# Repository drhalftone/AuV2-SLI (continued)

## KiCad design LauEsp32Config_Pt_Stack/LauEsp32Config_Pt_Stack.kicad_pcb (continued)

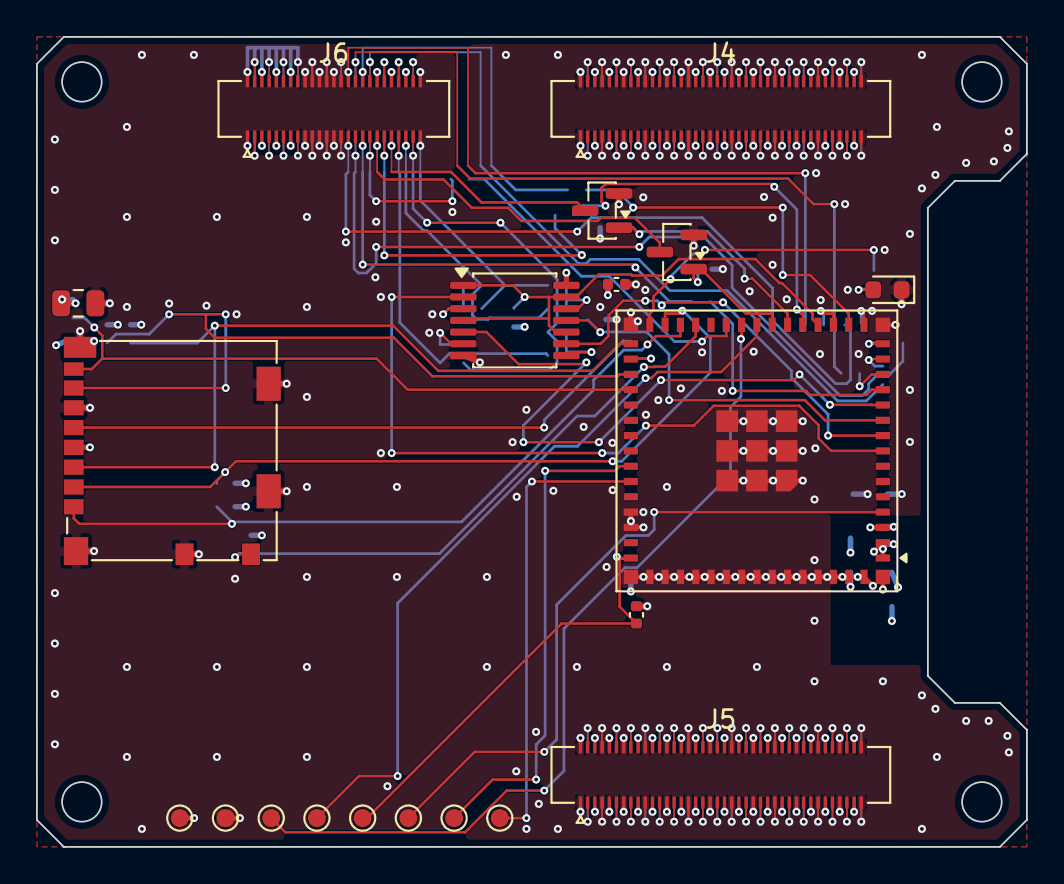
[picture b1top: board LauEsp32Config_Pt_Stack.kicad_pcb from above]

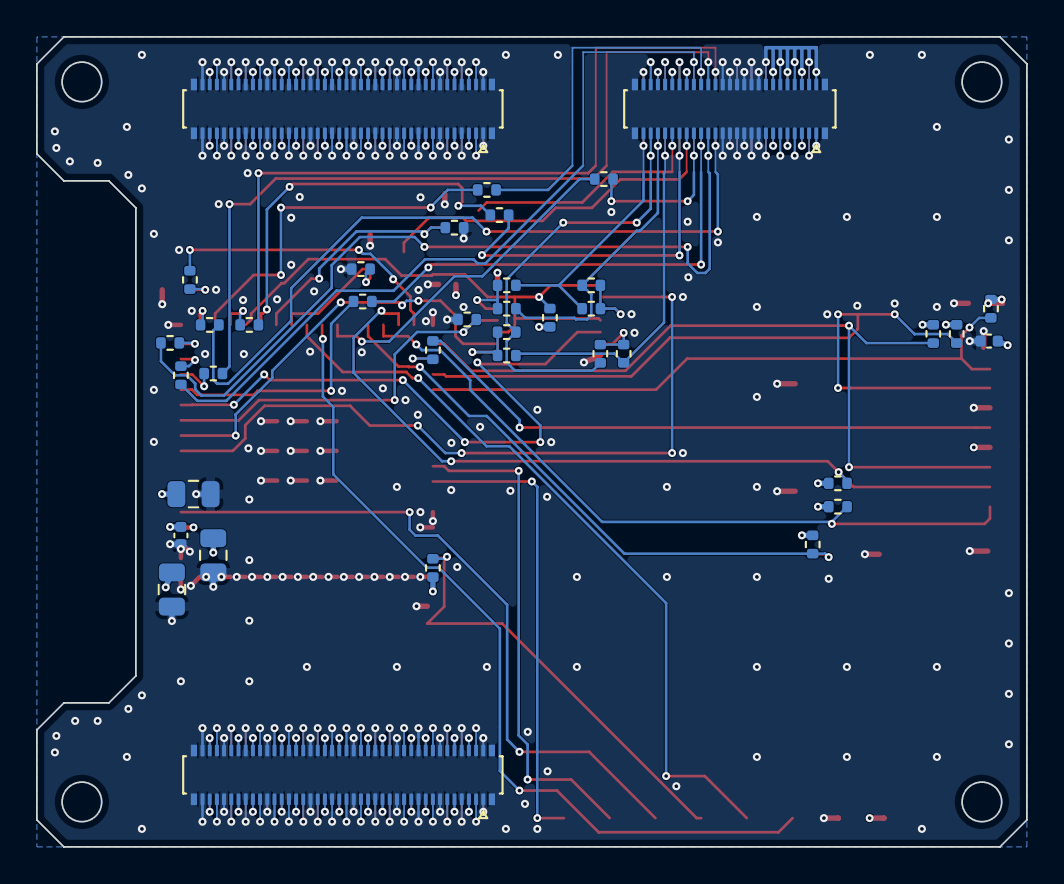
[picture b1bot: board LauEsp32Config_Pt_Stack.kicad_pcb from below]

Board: 4 copper layers, 55.0 x 45.0 mm, 58 parts (38 on the bottom side), 165 nets.

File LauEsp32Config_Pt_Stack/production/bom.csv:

Comment,Designator,Footprint,LCSC Part #
"22u","C1,C2",C_0805_2012Metric,C45783
"10u","C3,C7",C_0805_2012Metric,C15850
"100n","C4,C6,C8",C_0402_1005Metric,C1525
"1u","C5",C_0402_1005Metric,C52923
"Red","D1",LED_0603_1608Metric,C2286
"DF40C-80DP-0.4V(51)","J1,J2",Hirose_DF40C-80DP-0.4V_2x40-1MP_P0.4mm,C294544
"DF40C-50DP-0.4V(51)","J3",Hirose_DF40C-50DP-0.4V_2x25-1MP_P0.4mm,C424645
"DF40HC(4.0)-80DS-0.4V(51)","J4,J5",Hirose_DF40HC(4.0)-80DS-0.4V_2x40_P0.4mm,C5254351
"DF40HC(4.0)-50DS-0.4V(51)","J6",Hirose_DF40HC(4.0)-50DS-0.4V_2x25_P0.4mm,C5338326
"1040310811","J7",microSD_HC_Molex_104031-0811,C585350
"2N7002","Q1,Q2",SOT-23,C8545
"10k","R1,R2,R3,R4,R5,R31,R32,R33,R34,R35,R36",R_0402_1005Metric,C25744
"1k","R6,R7",R_0402_1005Metric,C11702
"0R","R10,R11,R12",R_0402_1005Metric,C17168
"33R","R13,R20,R21,R22,R23,R24,R25,R26,R27,R30",R_0402_1005Metric,C25105
"ESP32-S3-MINI-1U-N8","U1",ESP32-S2-MINI-1U,C2980299
"SN74LVC125APWR","U2",TSSOP-14_4.4x5mm_P0.65mm,C7813

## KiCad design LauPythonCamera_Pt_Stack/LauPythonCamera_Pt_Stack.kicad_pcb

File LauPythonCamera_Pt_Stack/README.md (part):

# LauPythonCamera_Pt_Stack — Design Blueprint

> **STATUS: the board works and is in the merged design.** The sensor is alive,
> aligned and streaming 1280x1024 at 120.000 Hz over the Ft+, concurrently with
> the HDMI/SLI datapath in one bitstream — see
> [`../MERGE_MILESTONES.md`](../MERGE_MILESTONES.md). This document remains the
> design blueprint for the PCB itself.
>
> Known hardware note: the Andon LCC48 socket is effectively unobtainable, so the
> sensor is held by a printed fixture clamping wires to the bottom castellations —
> see [`mech/README.md`](mech/README.md).

> ### Power: §§6.2 and 6.5 were rewritten on 2026-07-18 and now match the board.
>
> **[`../CAMERA_POWER_DESIGN.md`](../CAMERA_POWER_DESIGN.md) remains authoritative** for the
> power tree — full derivation, SPICE verification and BOM. This document is the design
> blueprint; where the two disagree, that one wins.
>
> **What changed, and why it matters historically.** The original power section described a
> "3.3 V tap through ferrites + load switch" tree, built on the premise that the Pt's `+3.3V`
> rail is 3.300 V. **It is 3.278 V** — derivable from Alchitry's own feedback divider
> (R16 = 31.6 kΩ / R15 = 10.2 kΩ into the ADP5052's 0.8 V reference), ±1.5 % → **3.229–3.327 V**.
> That broke the design three ways:
>
> - **`vdd_pix` (3.25–3.35 V) was out of spec** at the rail's low corner, by 21 mV.
> - **`vdd_33` had ~7 mV** of worst-case margin after ferrite and connector IR drop.
> - **The tap made correct power-up sequencing impossible.** `vdd_33` tapped from `+3V3` rises the
>   instant the Pt's rail does, but 1.8 V can only be made by LDO'ing *down from that same rail* —
>   so `vdd_18` always came up **after** `vdd_33`, the forbidden order, on every power-up. That
>   risks latch-up and a dead sensor.
>
> The board uses **boost → LDO**: `+3V3` → TPS61023 boost to 4.45 V → two TPS7A2033 LDOs for
> `vdd_33` and `vdd_pix`, `vdd_18` from a TPS7A2018 off `+3V3` directly, and **two TLV803S
> supervisors** enforcing power-up *and* power-down ordering. **There is no load switch and no
> ferrite on this board.** If you find text saying otherwise, it is stale — report it (§14.6).

Custom Alchitry **element board** carrying an onsemi **PYTHON 1300** global-shutter image
sensor in a **socketed 48-pin LCC**, for the AuV2-SLI structured-light system.

## Status

| | |
|---|---|
| Pin plan | ✅ **Confirmed by Vivado** (§13.1) |
| Whole stack — Pt V2 + Hd + Ft+ + camera | ✅ **Confirmed by Vivado** — 105 ports, no conflicts (§13.2) |
| Schematic | ⚠️ Complete and audited — but the **power tree was rebuilt from scratch** after an audit found it architecturally wrong (§6.5). **Deserves a human read before fab.** |
| Socket footprint | ✅ Built and verified (§12) — **no longer blocked** |
| Stackup / netclasses / DRC rules | ✅ Written (§11), and **calibrated against a real DRC run** (§14.7) |
| **Layout** | ✅ **Routed, reviewed (§14), DRC-clean (0 errors, 0 unconnected), and all three Tier 1 defects are FIXED** — re-verified against the board 2026-08-06. U1 decoupling closed by moving ten caps to the underside beneath the pins; power-section stitching now 13 GND vias; `+3V3_SYS` widened to 0.6 mm with the J3 pins fanned out. Six test points added. **Fab-ready** — two optional single-via redundancy items remain (§15.0), neither a blocker. |
| **Sensor + socket ordered** | ❌ **Do this first** — §15.1. Sensor: **~27-week** factory lead if distributor stock runs out — this is the critical path. Socket: **no stock anywhere**, Andon builds to order in **6–8 weeks**, so it is *not* the driver. |

**Eleven bugs have been found and fixed in this design so far**, including two that would have
destroyed the sensor and two that would have scrapped the board. Every one was a *boundary
crossed without re-deriving*: datasheet frame → KiCad frame, body extent → copper extent,
thermal question → voltage question, logic behaviour → electrical behaviour.

The FPGA side is tool-verified (§13). **The board side is verified only by my own arithmetic.**
The power section in particular has been rewritten and should be read by a human before copper.

---

## 1. What this board is for

The SLI system puts the FPGA **inline on HDMI between the host PC and the projector**
(hence the EDID-merge / HPD re-pulse logic in the main RTL). This board adds the *camera*
half: a 1.3 MP global-shutter sensor whose exposure can be synchronized to the projected
pattern sequence.

Because the camera must capture **in sync** with the projected patterns, HDMI pass-through
and camera capture run **simultaneously**. That constraint drives the entire pin plan below.

---

## 2. Board stack

```
   [ LauPythonCamera_Pt_Stack ]  <- THIS BOARD.  TOP, Bank B (B33-B78), bank 13, VCCO = 2.5 V
 ────────────────────────────────
          Alchitry Pt V2            XC7A100T-2FGG484I, 206 IO, 256 MB DDR3L
 ────────────────────────────────
   [ Sp ]    spacer — clears the Pt's bottom-side capacitors        $14.99
   [ Ft+ ]   bottom  A3-A42 + B3-B24   (3.3 V)   FT601Q USB3, 348 MB/s measured
   [ Sp ]    spacer — micro-HDMI / USB cable clearance              $14.99
   [ Hd  ]   bottom  A45-A78           (3.3 V)   2x micro-HDMI (PC in, projector out)
```

**This board goes on TOP, alone.** Rationale:

- The **Hd's signal pass-through is undocumented** and may terminate a stack. Keeping the
  camera on top means it never has to sit above the Hd, and **this board needs no
  pass-through connectors at all.**
- The 32 multi-voltage pins (the only ones that can run at 2.5 V) exist **only on the top**
  Bank-B connector. There are **zero** multi-voltage pins on the bottom. The camera
  therefore *must* be on top.

A `Br` ($14.99) may substitute for either `Sp`. **Do not use the `Fn`** — its fan-control
solder jumper lands on **B36, a bank-13 pin**, and would consume half of one of our LVDS
pairs.

---

## 3. Why the pin plan works — bank voltages

This is the crux of the design, and it was the one thing that could have sunk the stack.

| Consumer | IO standard | Required VCCO |
|---|---|---|
| Hd (HDMI TMDS) | `TMDS_33` | **3.3 V** |
| Ft+ (FT601 FIFO) | `LVCMOS33` | **3.3 V** |
| **This board (sensor LVDS)** | **`LVDS_25`** | **2.5 V** |

An FPGA bank has exactly one VCCO, so these had to land in different banks. On the Pt V2
they do:

| Bank | VCCO | Pins |
|---|---|---|
| 14, 16, 34, 35 | **hardwired 3.3 V** | Hd and Ft+ live here |
| 15 | 1.35 V | DDR3L (internal) |
| **13** | **switchable 3.3 / 2.5 / 1.8 V** | **top Bank B, B33-B78 — 32 pins / 16 pairs — ALL OURS** |

**Neither the Hd nor the Ft+ places a single pin in bank 13.** Verified against Alchitry's
own constraint sources (`ft_plus_v2.acf`, `hd_v2.acf`, `PtV2TopPin.kt`) and cross-checked
against the official `pt_hd_bottom.xdc` / `pt_ft_plus_bottom.xdc`. The product pages do not
contain this information.

The Ft+ (A3-A42 + B3-B24) and the Hd (A45-A78) are also **mutually disjoint** — they are
designed to coexist. Their only conflict is mechanical (cable clearance), solved by the `Sp`.

### LVDS_25 nuance that forces bank 13

An `LVDS_25` **input** with *external* 100 Ω termination imposes no VCCO requirement and
would work in a 3.3 V bank. But:

- an `LVDS_25` **output** — which we need, to drive `lvds_clock_in±` **into** the sensor — and
- any input using the FPGA's **internal `DIFF_TERM`**

both **require VCCO = 2.5 V**. So bank 13 is mandatory regardless of how we terminate.

> **DANGER.** Alchitry: *"Failing to set the tri-voltage pins correctly could damage the
> FPGA."* See the VBSEL strapping in §6.

---

## 4. Sensor

> **Now fitted (2026-10):** the **colour** `NOIP1SE1300A` (Bayer), in the Andon socket. Same pinout,
> same chip ID (`0x50D0`); the only boot difference is register 2 = `0x0001`.

**`NOIP1SN1300A-QTI`** — PYTHON 1300, monochrome, 4-LVDS output, 48-pin LCC. *(The
originally-specified `-QDI` is discontinued; `-QTI` is the identical sensor with a peel-off
protective foil over the glass — see the ordering note below.)*

| | |
|---|---|
| Resolution / rate | 1280 x 1024, 10-bit, **150 fps** (sensor max; we run a locked **120 Hz** — see *Operating point*) |
| Pixel | 4.8 x 4.8 µm, global shutter |
| Package | 48-pin LCC, **14.22 x 14.22 mm, 1.016 mm pitch**, D263 glass lid |
| Output | 4 LVDS data + 1 LVDS sync + 1 LVDS clock out; 720 Mbps/ch |
| Supplies | `vdd_33` 3.3 V, `vdd_18` 1.8 V, `vdd_pix` 3.3 V (tight: 3.25-3.35 V) |
| Price / lead | ~$139, long factory lead — order early |

**The VITA 1300 (`NOIV1SN1300A`) is pin-for-pin identical** — all 48 pins, both LVDS and
parallel variants — so this board accepts either. PYTHON is preferred: faster, and the VITA
datasheet carries a *"no silicon fix planned"* erratum (first-row blooming, costing 5 rows).

Design the rails to **PYTHON's tighter tolerances** so either part drops in.

> **Order the `-QTI` suffix.** The originally-specified `-QDI` (no protective foil) has been
> discontinued. `-QTI` is the identical PYTHON 1300 sensor but ships with a **peel-off
> protective foil** over the glass — remove it before installing the sensor (handle the glass
> by the edges afterward). The foil is otherwise harmless handling protection, and a bonus:
> its tab points toward pin 1 — a useful orientation aid, since the package has no chamfer/dot (§12).

### Bandwidth check

```
1280 x 1024 x 10 bit x 150 fps  =  245.8 MB/s
Ft+ (FT601Q), BARE LINK 2026-07-31 = 348   MB/s     ->  pattern generator only
Ft+ (FT601Q), END-TO-END 2026-08-17 = 232  MB/s     ->  with camera + DDR running
Ft  (FT600),  datasheet estimate  =  190   MB/s     ->  does NOT fit
```

> **THE TWO Ft+ NUMBERS MEASURE DIFFERENT THINGS, and only one of them is a budget.**
> 348 MB/s is the FT601 fed by a pattern generator — no camera, no DDR, nothing
> competing. With the real pipeline running, the *same* `ft_bench_async.py` measures
> **231.7 MB/s**, because the reader is now sharing one MIG port with the capture
> writer. Sampled while saturated, both ends were at their limit at once: the DDR→USB
> FIFO ran dry 32 % of the time **and** the FT601 back-pressured 40 %.
>
> **Budget against ~232 MB/s.** Using 348 led directly to a build that targeted 120 Hz
> at 16 bpp (314.6 MB/s "with ~10 % margin") and delivered **88 fps**.
>
> The Ft (FT600) number is still an estimate — not measured here.

### Operating point — ACHIEVED 2026-08-17

**1280 × 1024, packed 10-bit, locked 120.000 Hz, exposure settable at runtime.**

```
capture     120.000 Hz   (600,000 wordclk cycles, +/-2 cycles jitter -> ~3 ppm)
delivered   119.8 fps    201 MB/s, 25 CLEAN / 0 padded, ldrop static at 0
alignment   10 of 10 frames agree, r = 1.000
exposure    monotonic 75 us -> 4800 us, no saturation, independent of frame rate
```

Three things had to be true at once, and each was a separate fault:

1. **Dense 10-bit packing** (format 3, 4 px in 5 bytes). At 16 bpp a 120 Hz frame costs
   314.6 MB/s against ~232 available; packed it costs **196.6 MB/s**. 37.5 % of every
   byte moved had been zero padding. Packing goes all the way into DDR, not just onto
   the wire — otherwise the reader still pulls 314.6 MB/s out of DDR, which is the side
   that was already starving.
2. **Frame-start resync in the DDR writer.** Without it, one lost kernel repositioned
   every frame that followed, permanently — the picture rolled in both axes.
3. **The trigger pulse width.** `TRIGGERED=1` paced the sensor at a perfect 120.000 Hz
   while delivering *no pixels at all*, because the pulse width came from an
   **exposure-sweep experiment table that was never gated on `EXPO_SWEEP`**. It cycled
   50 → 6400 µs every eight frames, and 6.4 ms of integration plus 6.86 ms of readout
   does not fit in an 8.33 ms period. It also meant exposure was set by pulse width, so
   `exposure0` did nothing in triggered mode. The trigger is now a fixed 10 µs
   frame-start marker and the sensor integrates for `exposure0`.

#### Usable exposure range at 120 Hz — and a state that needs a reflash to escape

**Maximum exposure is 8243 µs, and the boundary is a cliff, not a slope.** The sensor
cannot integrate for a whole frame period *and* still answer the next trigger, so past
the limit it wedges. Measured against the DELIVERED rate:

```
2026-10-07, with the CDS timing program loaded (the current sensor configuration):
 600..8254 us   121 fps       full rate
      8256 us     0.0 fps     wedges            -> the sensor needs ~78 us after an exposure

before 2026-10-05, without it (kept for history -- NOT valid now):
 600..8280 us   111-122 fps   full rate, ldrop 0 at every setting
      8300 us      0.0 fps    collapses
      8333 us     59.8 fps    every other trigger missed
```

The old 8280 µs figure wedged the sensor once the CDS program went in. The limit is now
`period − 80 µs − 10 µs` (`usb_link.v` publishes it as MAXEXP; `cam_expo_safety.v` enforces it).

> **The status UART cannot see this.** It reports a healthy 120.00 Hz throughout,
> because the FPGA goes on triggering whether or not the sensor answers. Only the
> delivered byte rate shows the truth — the same trap as the throughput-vs-bytes
> lesson in [`ROADMAP.md`](../ROADMAP.md) §6.

> **⚠️ OVER-EXPOSING WEDGES THE SENSOR.** After one setting above the cliff, restoring a
> valid exposure did NOT recover it: `expo_cur` read back correctly and frame_start kept
> arriving at 120.000 Hz, but no frame ever completed (`rdBusy = 0`) and no bytes
> reached USB. A re-arm (opcode 3) did not help either. It took a full FPGA reconfigure
> to re-run the sensor's SPI boot sequence. That is why the cap is now **enforced in the
> FPGA** (`ddr/cam_expo_safety.v`): every exposure command is clamped, the exposure is
> shortened when the rate rises, and the trigger is held while a longer exposure may still
> be in effect. `cam_live.py` takes its slider top from the FPGA's MAXEXP.

> **The 120 Hz is the right RATE but not a locked PHASE.** The trigger comes from the
> FPGA's own 100 MHz crystal, so it drifts against a projector on a different
> oscillator. For structured light that drift is the whole problem — see
> [`ROADMAP.md`](../ROADMAP.md) §6.5 for the external-HDMI-sync plan (vsync-derived
> trigger with a user-programmable phase shift), and the wiring question that gates it.

The Ft+ is **mandatory**. The Ft cannot carry full-rate capture, and the Pt V2's onboard
FT2232HQ is USB 2.0 (JTAG/UART only) — not a data path.

---

## 5. Pin plan

<!-- PIN_TABLE_START -->

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
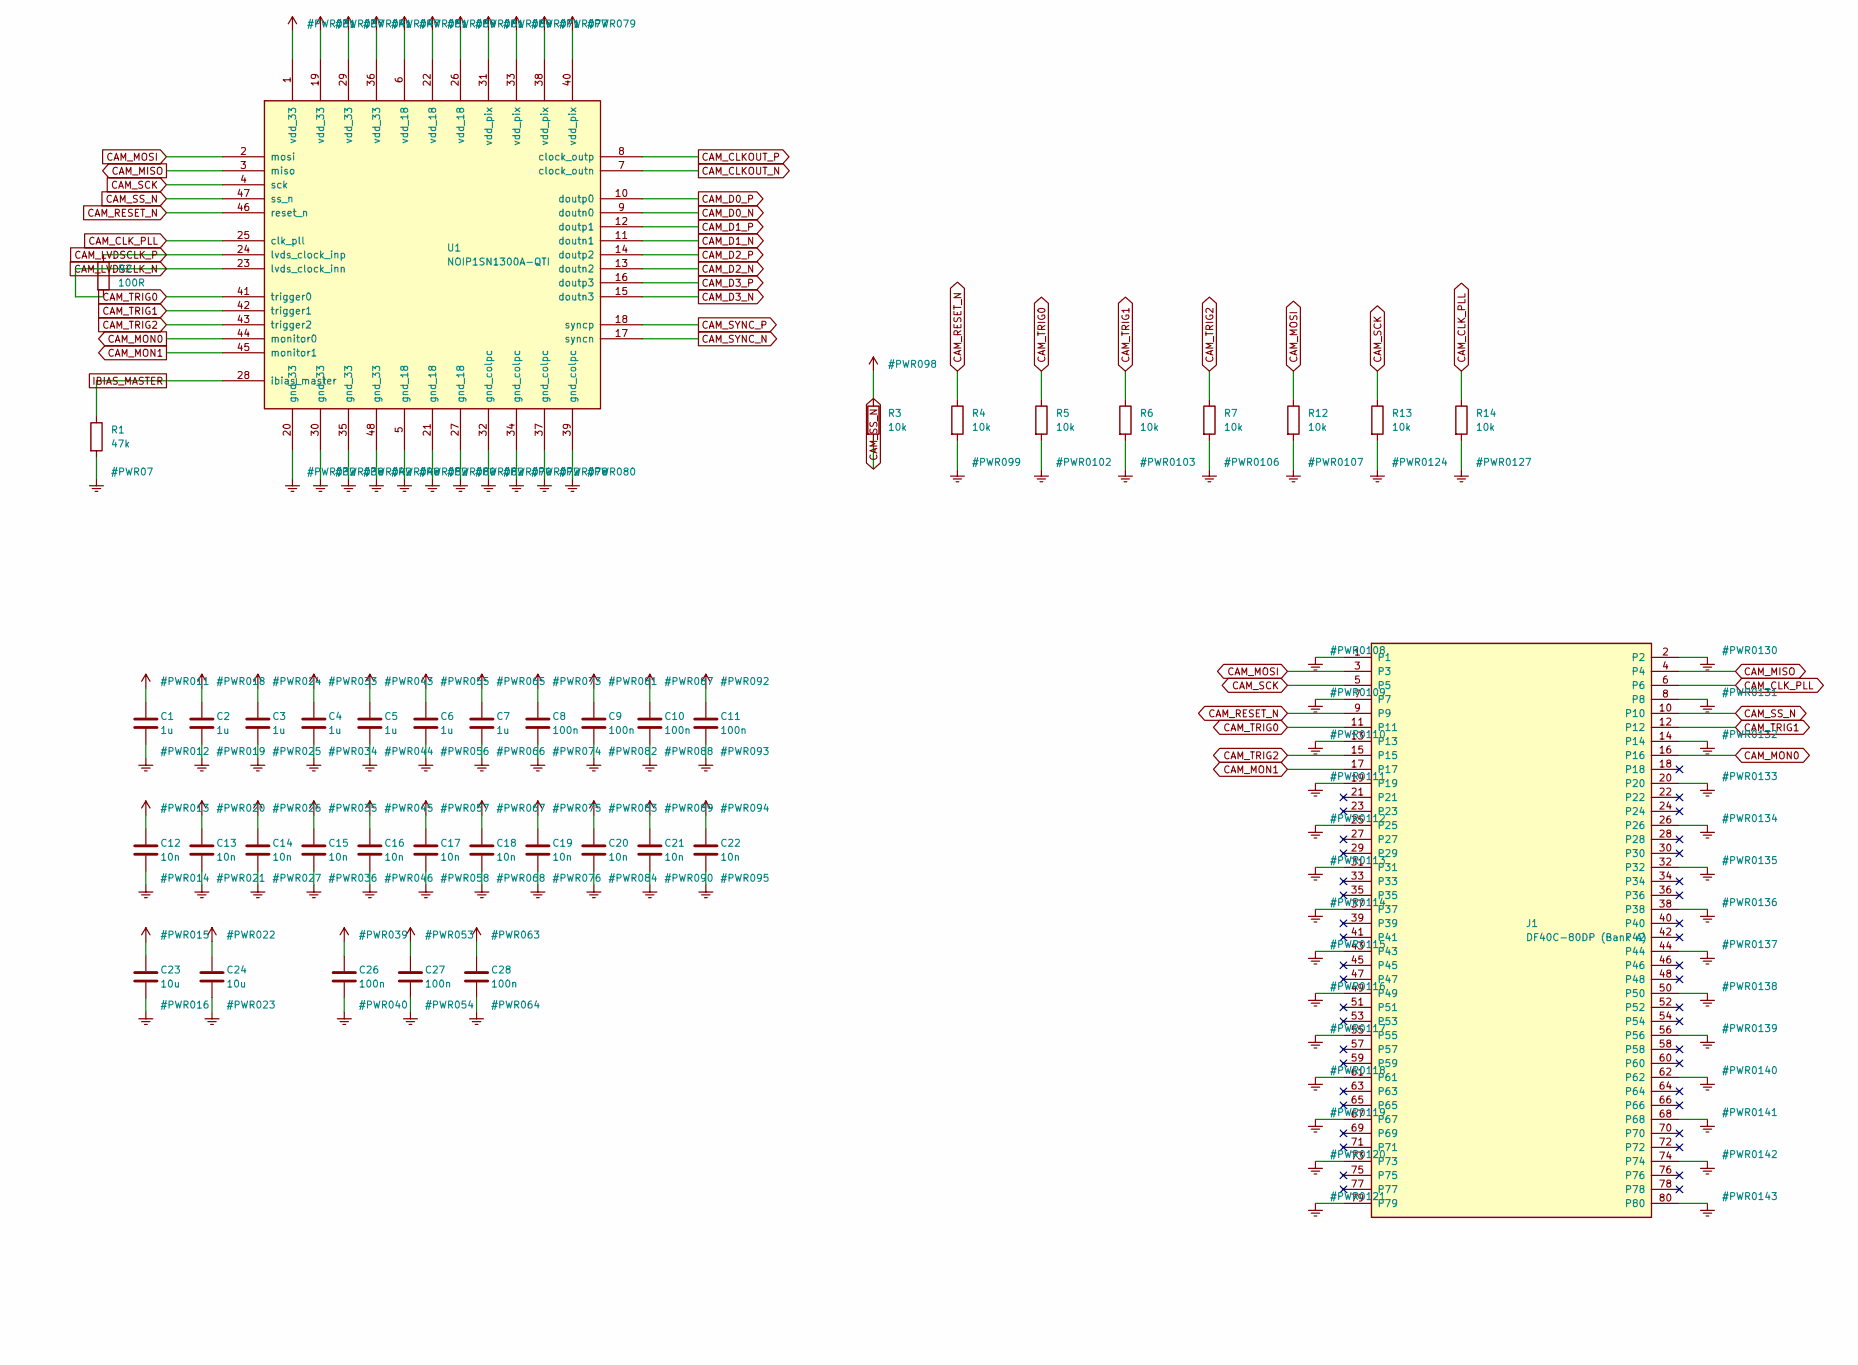
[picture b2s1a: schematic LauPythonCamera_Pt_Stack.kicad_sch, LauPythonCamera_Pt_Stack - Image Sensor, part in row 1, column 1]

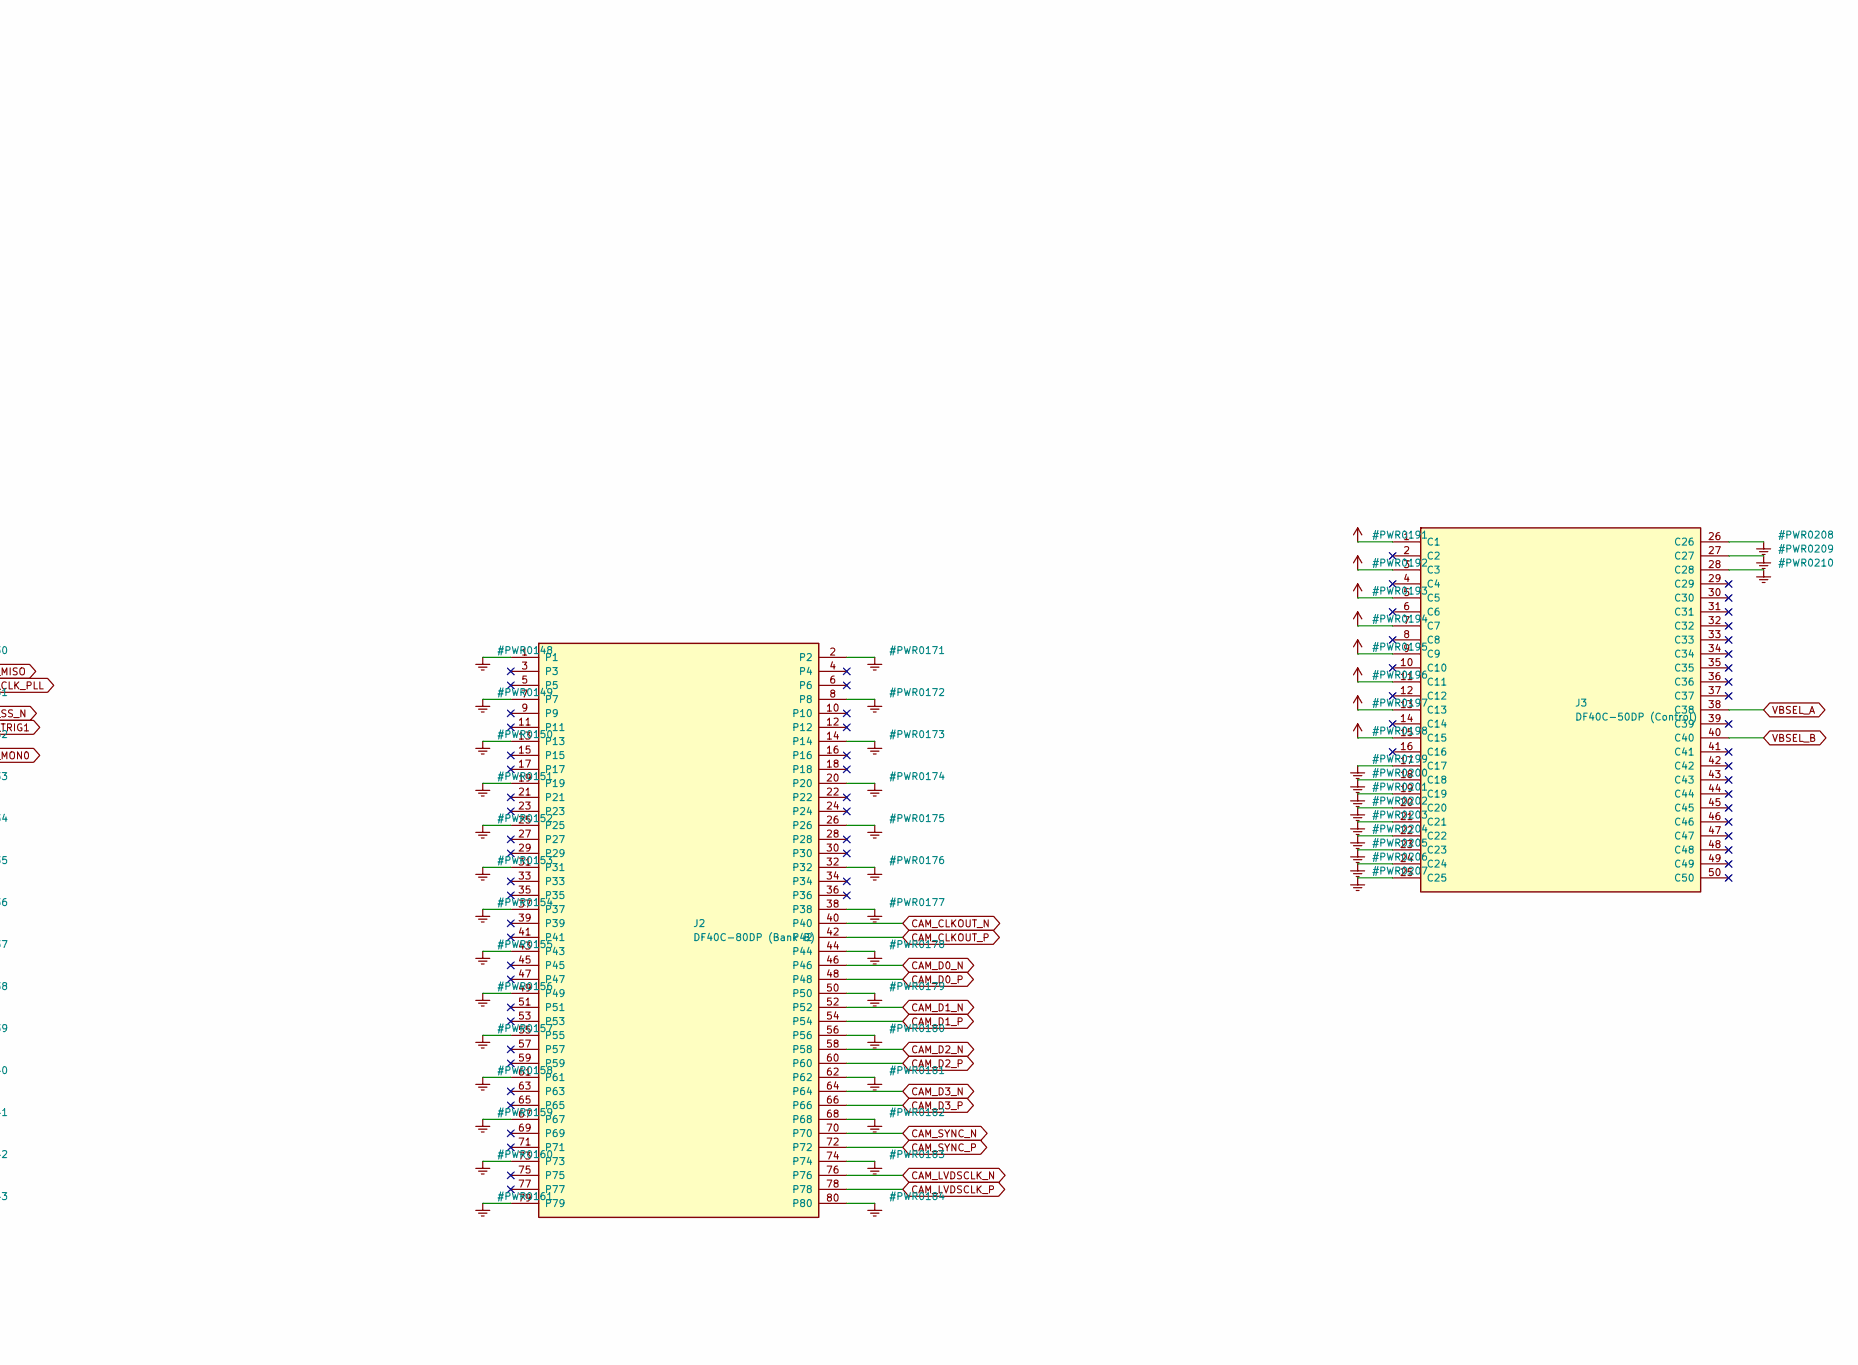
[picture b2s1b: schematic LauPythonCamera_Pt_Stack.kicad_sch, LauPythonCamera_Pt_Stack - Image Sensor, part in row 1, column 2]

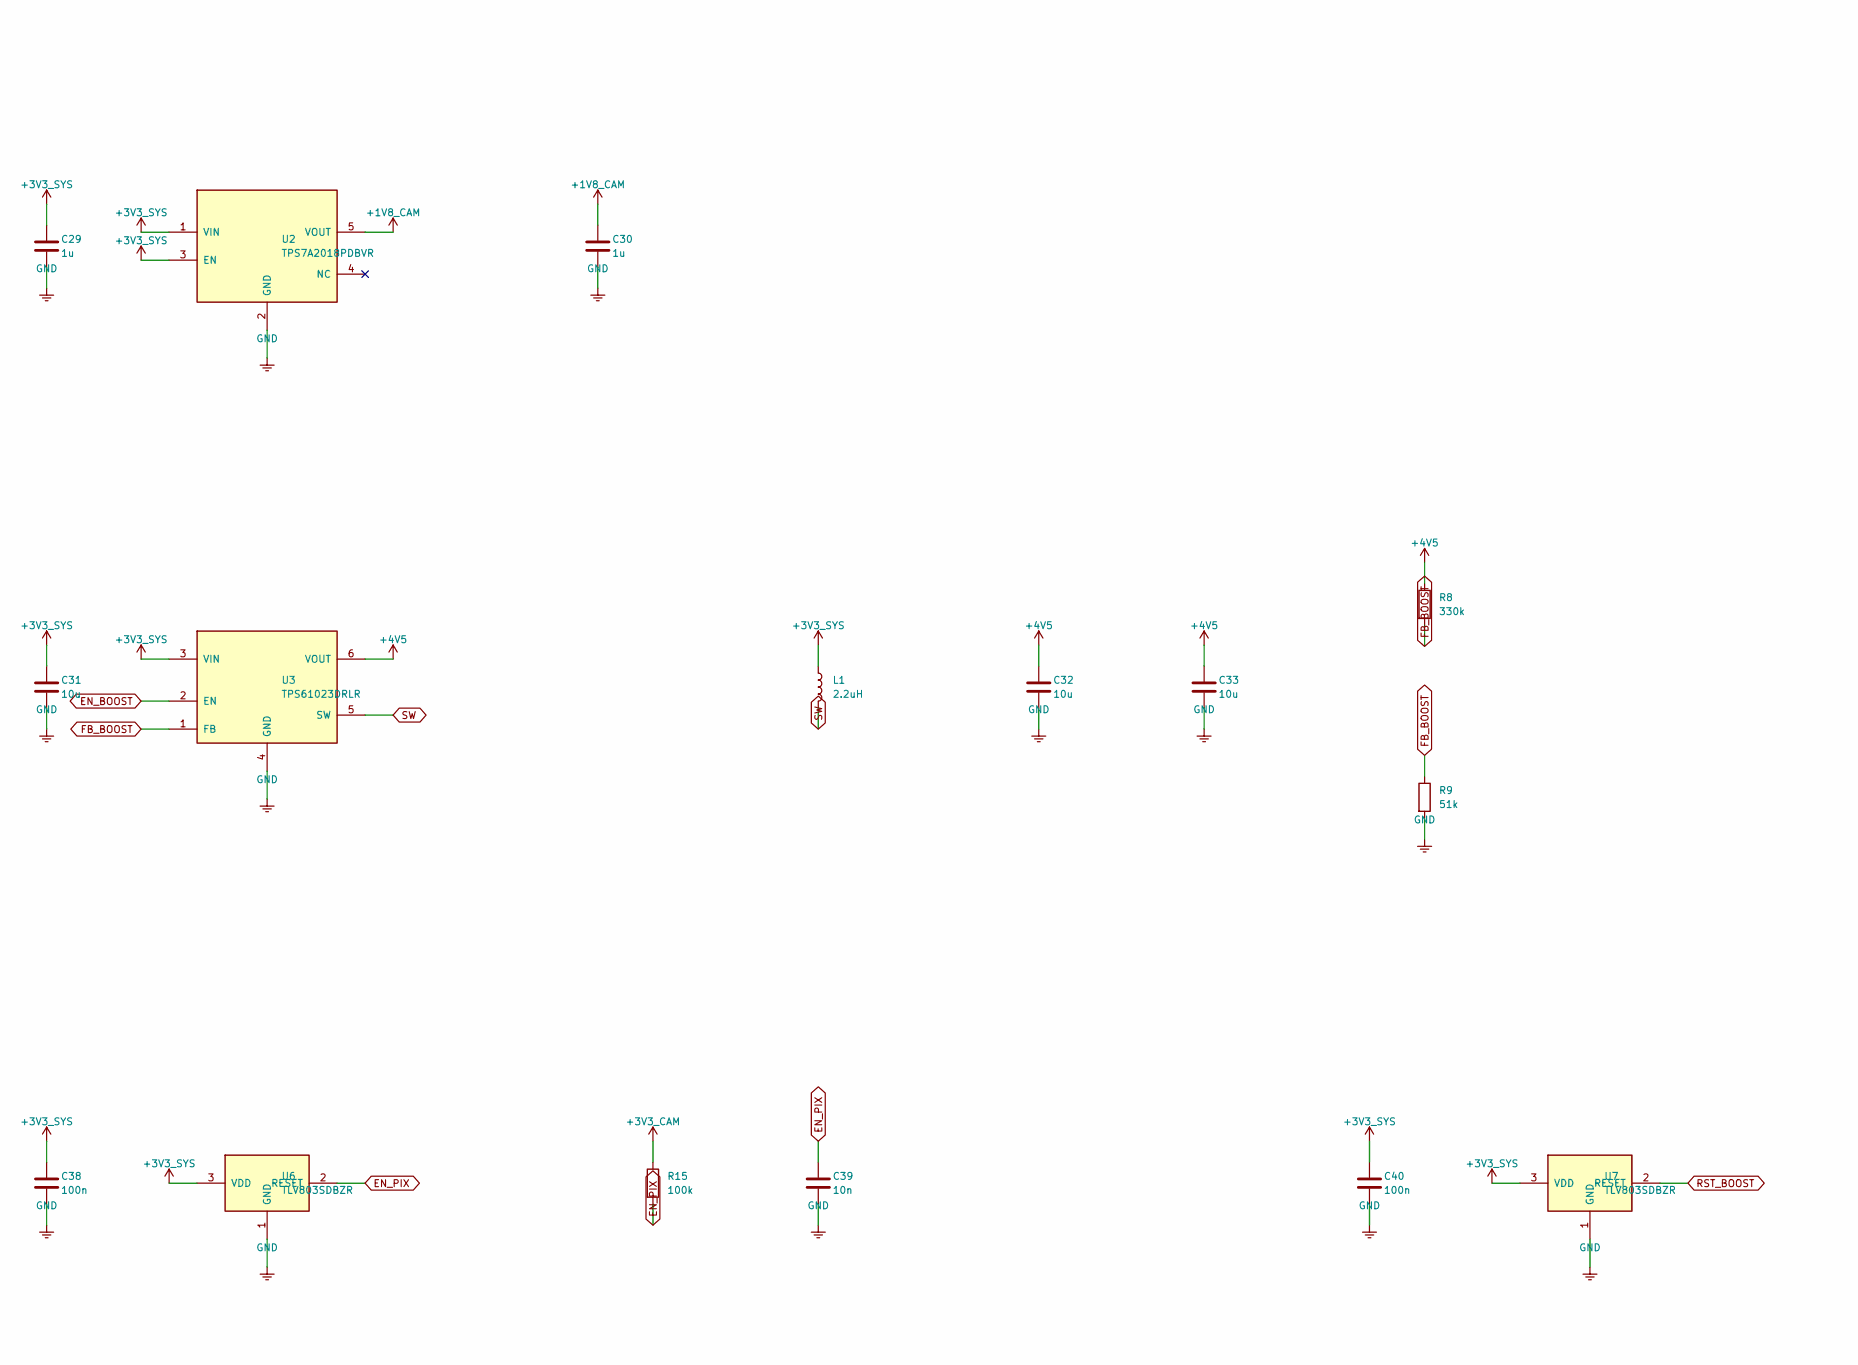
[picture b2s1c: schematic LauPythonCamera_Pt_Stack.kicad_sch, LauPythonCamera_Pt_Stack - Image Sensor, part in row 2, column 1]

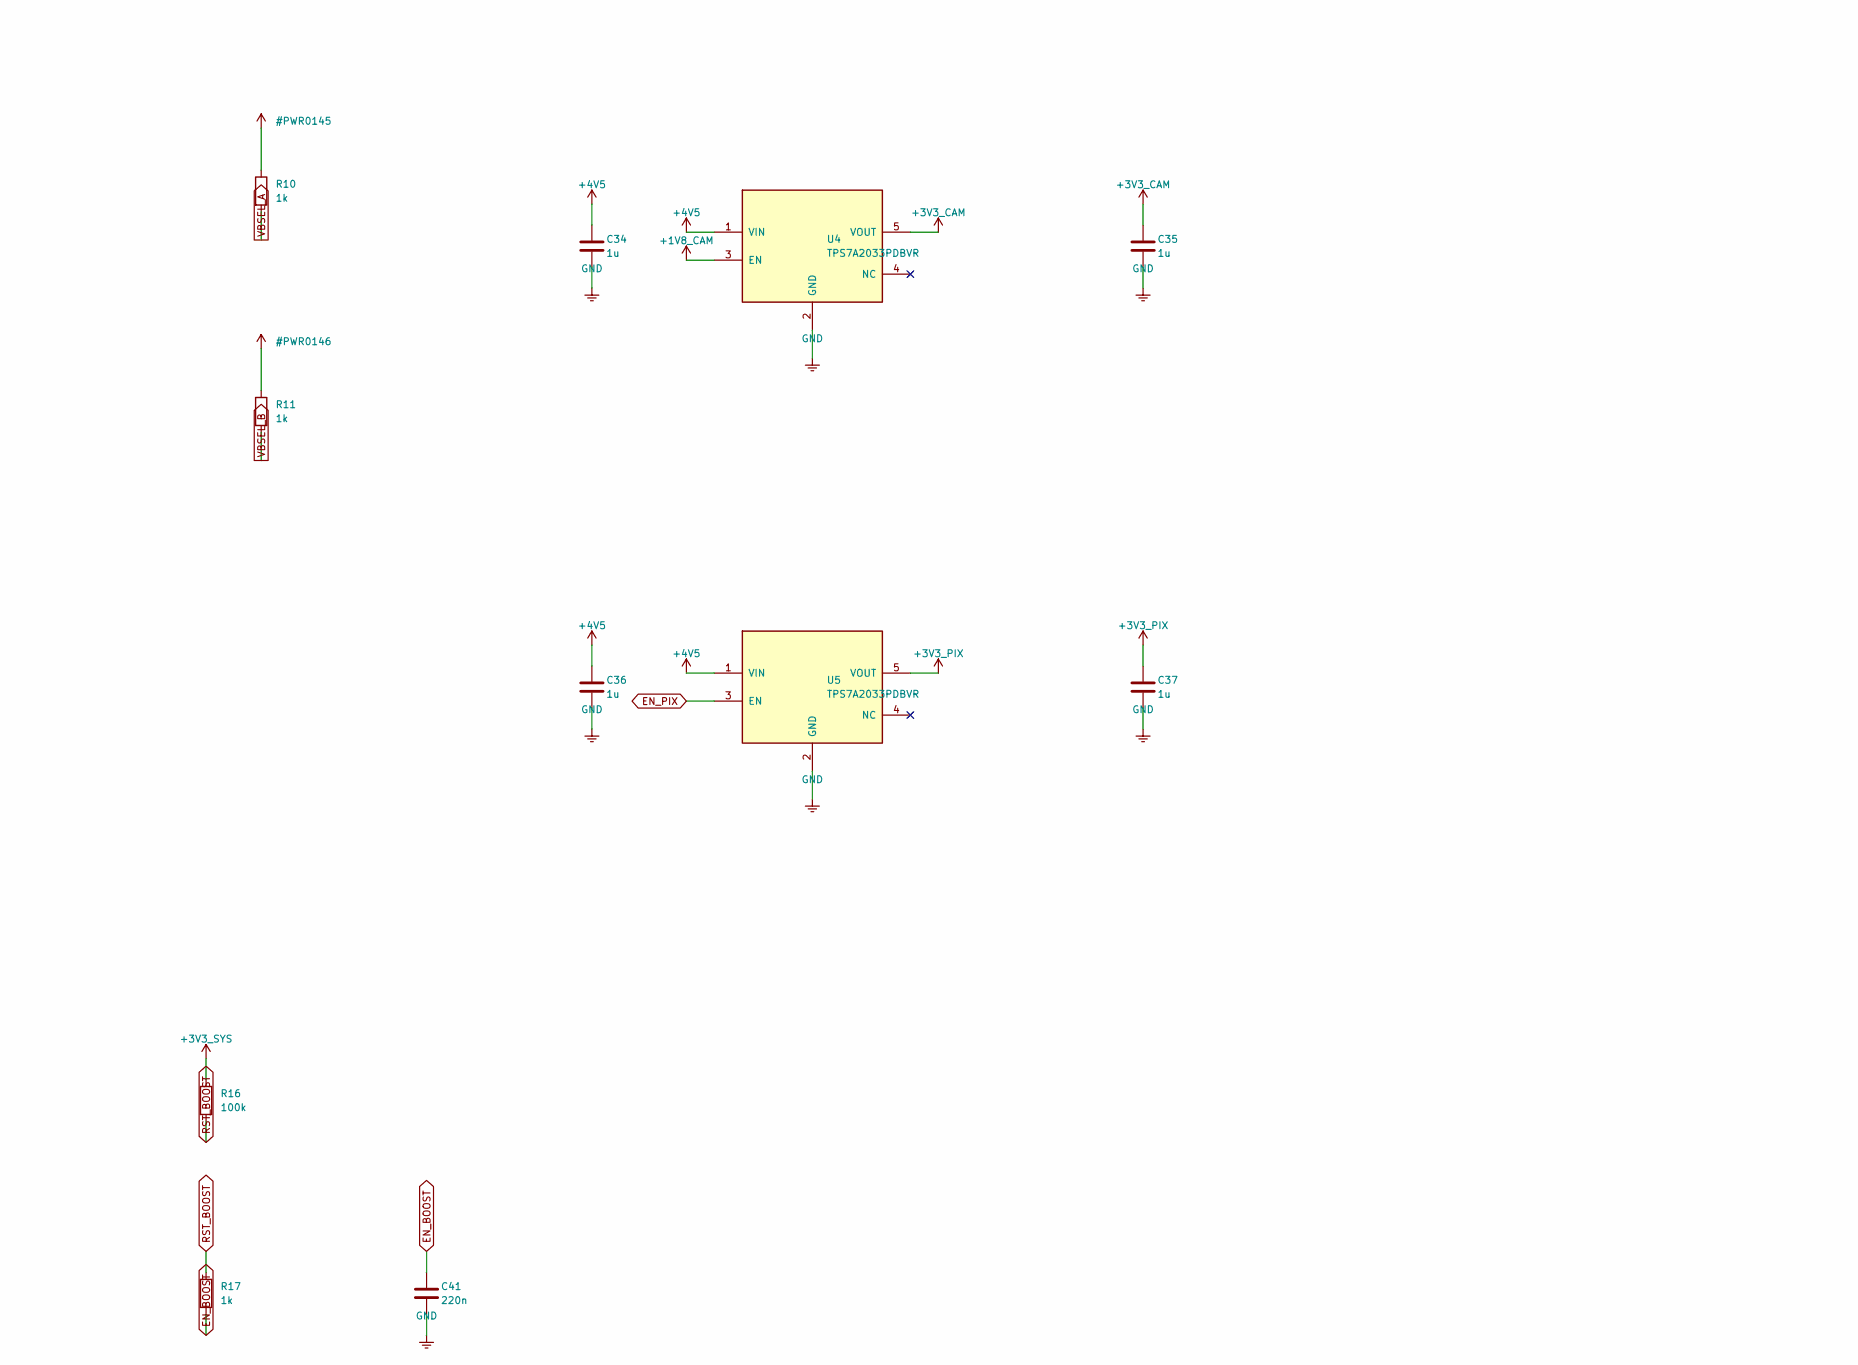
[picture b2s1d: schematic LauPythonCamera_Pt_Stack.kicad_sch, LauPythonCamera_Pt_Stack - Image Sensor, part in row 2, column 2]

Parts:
C1, C2, C3, C4, C5, C6, C7: 1u; C_0402_1005Metric; MPN CL05A105KA5NQNC; LCSC C52923
C8, C9, C10, C11, C26, C27, C28, C38, C40: 100n; C_0402_1005Metric; MPN CL05B104KO5NNNC; LCSC C1525
C12, C13, C14, C15, C16, C17, C18, C19, C20, C21, C22, C39: 10n; C_0402_1005Metric; MPN CL05B103KB5NNNC; LCSC C15195
C23, C24, C31, C32, C33: 10u; C_0805_2012Metric; MPN CL21A106KAYNNNE; LCSC C15850
C29, C30, C34, C35, C36, C37: 1u; C_0603_1608Metric; MPN CL10A105KB8NNNC; LCSC C15849
C41: 220n; C_0402_1005Metric; MPN CL05B224KO5NNNC; LCSC C16772
J1: DF40C-80DP (Bank A); Hirose_DF40C-80DP-0.4V_2x40-1MP_P0.4mm; MPN DF40C-80DP-0.4V(51); LCSC C294544
J2: DF40C-80DP (Bank B); Hirose_DF40C-80DP-0.4V_2x40-1MP_P0.4mm; MPN DF40C-80DP-0.4V(51); LCSC C294544
J3: DF40C-50DP (Control); Hirose_DF40C-50DP-0.4V_2x25-1MP_P0.4mm; MPN DF40C-50DP-0.4V(51); LCSC C424645
L1: 2.2uH; L_Power_4x4mm_SMNR4020; MPN SMNR4020-2.2UH; LCSC C135262
R1: 47k; R_0402_1005Metric; MPN 0402WGF4702TCE; LCSC C25792
R2: 100R; R_0402_1005Metric; MPN 0402WGF1000TCE; LCSC C25076
R3, R4, R5, R6, R7, R12, R13, R14: 10k; R_0402_1005Metric; MPN 0402WGF1002TCE; LCSC C25744
R8: 330k; R_0402_1005Metric; MPN 0402WGF3303TCE; LCSC C25778
R9: 51k; R_0402_1005Metric; MPN 0402WGF5102TCE; LCSC C25794
R10, R11, R17: 1k; R_0402_1005Metric; MPN 0402WGF1001TCE; LCSC C11702
R15, R16: 100k; R_0402_1005Metric; MPN 0402WGF1003TCE; LCSC C25741
U1: NOIP1SN1300A-QTI; Andon_680-48-SM-G10-R14; MPN 680-48-SM-G10-R14-1
U2: TPS7A2018PDBVR; SOT-23-5; MPN TPS7A2018PDBVR; LCSC C963430
U3: TPS61023DRLR; SOT-563; MPN TPS61023DRLR; LCSC C919459
U4, U5: TPS7A2033PDBVR; SOT-23-5; MPN TPS7A2033PDBVR; LCSC C2862740
U6, U7: TLV803SDBZR; SOT-23; MPN TLV803SDBZR; LCSC C132016

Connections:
+1V8_CAM: C5.1, C6.1, C7.1, C16.1, C17.1, C18.1, C24.1, C27.1, C30.1, U1.6 (vdd_18), U1.22 (vdd_18), U1.26 (vdd_18), U2.5 (VOUT), U4.3 (EN); also elsewhere on the board
+3V3_CAM: C1.1, C2.1, C3.1, C4.1, C12.1, C13.1, C14.1, C15.1, C23.1, C26.1, C35.1, R3.1, R15.1, U1.1 (vdd_33), U1.19 (vdd_33), U1.29 (vdd_33), U1.36 (vdd_33), U4.5 (VOUT); also elsewhere on the board
+3V3_PIX: C8.1, C9.1, C10.1, C11.1, C19.1, C20.1, C21.1, C22.1, C28.1, C37.1, U1.31 (vdd_pix), U1.33 (vdd_pix), U1.38 (vdd_pix), U1.40 (vdd_pix), U5.5 (VOUT); also elsewhere on the board
+3V3_SYS: C29.1, C31.1, C38.1, C40.1, J3.1 (C1), J3.3 (C3), J3.5 (C5), J3.7 (C7), J3.9 (C9), J3.11 (C11), J3.13 (C13), J3.15 (C15), L1.1, R10.1, R11.1, R16.1, U2.1 (VIN), U2.3 (EN), U3.3 (VIN), U6.3 (VDD), U7.3 (VDD); also elsewhere on the board
+4V5: C32.1, C33.1, C34.1, C36.1, R8.1, U3.6 (VOUT), U4.1 (VIN), U5.1 (VIN); also elsewhere on the board
CAM_CLKOUT_N: J2.40, U1.7 (clock_outn)
CAM_CLKOUT_P: J2.42, U1.8 (clock_outp)
CAM_CLK_PLL: J1.6, R14.1, U1.25 (clk_pll)
CAM_D0_N: J2.46, U1.9 (doutn0)
CAM_D0_P: J2.48, U1.10 (doutp0)
CAM_D1_N: J2.52, U1.11 (doutn1)
CAM_D1_P: J2.54, U1.12 (doutp1)
CAM_D2_N: J2.58, U1.13 (doutn2)
CAM_D2_P: J2.60, U1.14 (doutp2)
CAM_D3_N: J2.64, U1.15 (doutn3)
CAM_D3_P: J2.66, U1.16 (doutp3)
CAM_LVDSCLK_N: J2.76, R2.2, U1.23 (lvds_clock_inn)
CAM_LVDSCLK_P: J2.78, R2.1, U1.24 (lvds_clock_inp)
CAM_MISO: J1.4, U1.3 (miso)
CAM_MON0: J1.16, U1.44 (monitor0)
CAM_MON1: J1.17, U1.45 (monitor1)
CAM_MOSI: J1.3, R12.1, U1.2 (mosi)
CAM_RESET_N: J1.9, R4.1, U1.46 (reset_n)
CAM_SCK: J1.5, R13.1, U1.4 (sck)
CAM_SS_N: J1.10, R3.2, U1.47 (ss_n)
CAM_SYNC_N: J2.70, U1.17 (syncn)
CAM_SYNC_P: J2.72, U1.18 (syncp)
CAM_TRIG0: J1.11, R5.1, U1.41 (trigger0)
CAM_TRIG1: J1.12, R6.1, U1.42 (trigger1)
CAM_TRIG2: J1.15, R7.1, U1.43 (trigger2)
EN_BOOST: C41.1, R17.2, U3.2 (EN)
EN_PIX: C39.1, R15.2, U5.3 (EN), U6.2 (RESET)
FB_BOOST: R8.2, R9.1, U3.1 (FB)
GND: C1.2, C2.2, C3.2, C4.2, C5.2, C6.2, C7.2, C8.2, C9.2, C10.2, C11.2, C12.2, C13.2, C14.2, C15.2, C16.2, C17.2, C18.2, C19.2, C20.2, C21.2, C22.2, C23.2, C24.2, C26.2, C27.2, C28.2, C29.2, C30.2, C31.2, C32.2, C33.2, C34.2, C35.2, C36.2, C37.2, C38.2, C39.2, C40.2, C41.2, J1.1, J1.2, J1.7, J1.8, J1.13, J1.14, J1.19, J1.20, J1.25, J1.26, J1.31, J1.32, J1.37, J1.38, J1.43, J1.44, J1.49, J1.50, J1.55, J1.56, J1.61, J1.62, J1.67, J1.68, J1.73, J1.74, J1.79, J1.80, J2.1, J2.2, J2.7, J2.8, J2.13, J2.14, J2.19, J2.20, J2.25, J2.26, J2.31, J2.32, J2.37, J2.38, J2.43, J2.44, J2.49, J2.50, J2.55, J2.56, J2.61, J2.62, J2.67, J2.68, J2.73, J2.74, J2.79, J2.80, J3.17 (C17), J3.18 (C18), J3.19 (C19), J3.20 (C20), J3.21 (C21), J3.22 (C22), J3.23 (C23), J3.24 (C24), J3.25 (C25), J3.26 (C26), J3.27 (C27), J3.28 (C28), R1.2, R4.2, R5.2, R6.2, R7.2, R9.2, R12.2, R13.2, R14.2, U1.5 (gnd_18), U1.20 (gnd_33), U1.21 (gnd_18), U1.27 (gnd_18), U1.30 (gnd_33), U1.32 (gnd_colpc), U1.34 (gnd_colpc), U1.35 (gnd_33), U1.37 (gnd_colpc), U1.39 (gnd_colpc), U1.48 (gnd_33), U2.2 (GND), U3.4 (GND), U4.2 (GND), U5.2 (GND), U6.1 (GND), U7.1 (GND); also elsewhere on the board
IBIAS_MASTER: R1.1, U1.28 (ibias_master)
RST_BOOST: R16.2, R17.1, U7.2 (RESET)
SW: L1.2, U3.5 (SW)
VBSEL_A: J3.38 (C38), R10.2
VBSEL_B: J3.40 (C40), R11.2

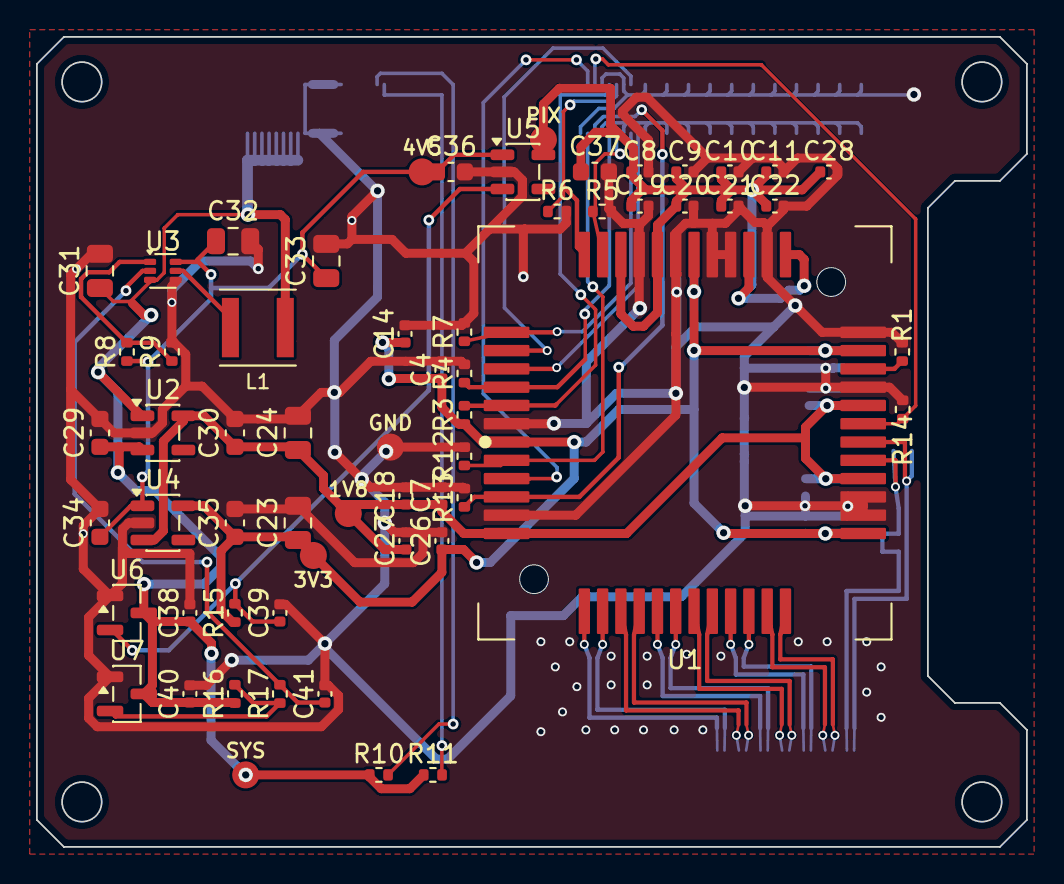
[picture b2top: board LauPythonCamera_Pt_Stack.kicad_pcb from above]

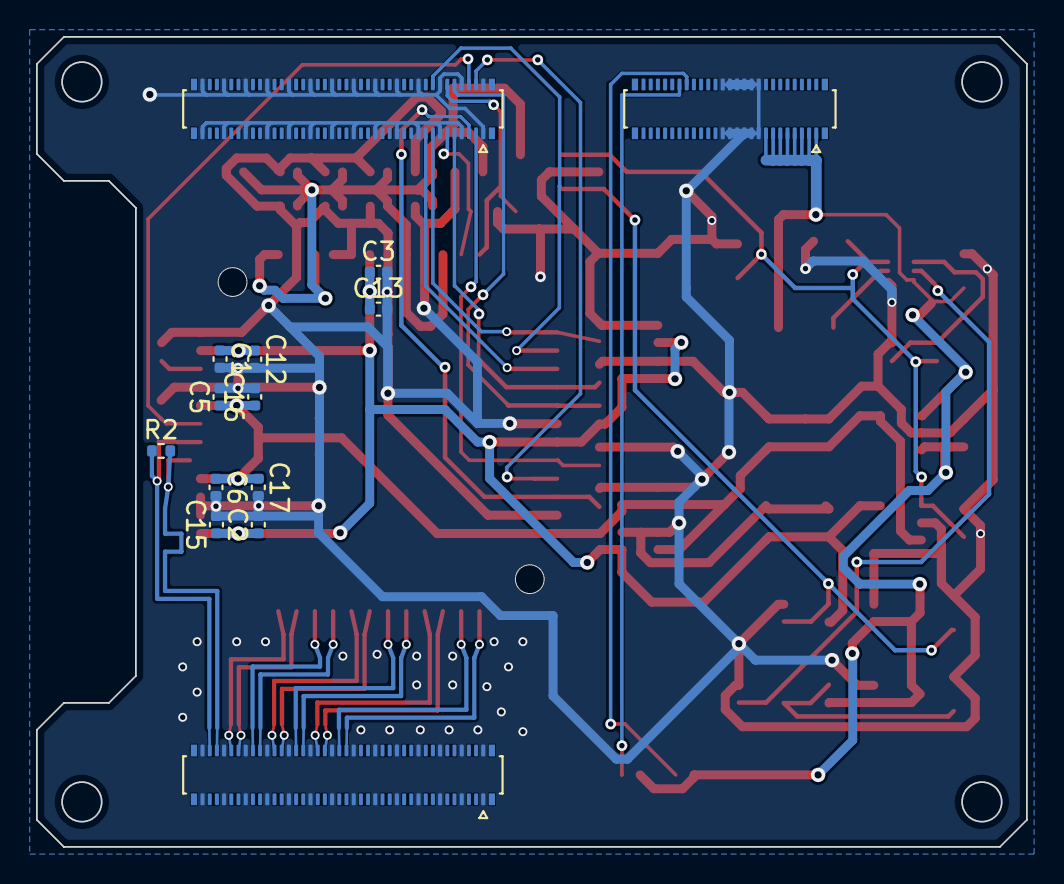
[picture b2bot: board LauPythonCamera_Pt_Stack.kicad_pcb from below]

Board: 4 copper layers, 55.0 x 45.0 mm, 74 parts (14 on the bottom side), 39 nets.

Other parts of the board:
TP1: SYS; TestPoint_Pad_D1.5mm
TP2: 4V5; TestPoint_Pad_D1.5mm
TP3: 1V8; TestPoint_Pad_D1.5mm
TP4: 3V3; TestPoint_Pad_D1.5mm
TP5: PIX; TestPoint_Pad_D1.5mm
TP6: GND; TestPoint_Pad_D1.5mm

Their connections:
+1V8_CAM: TP3.1; also elsewhere on the board
+3V3_CAM: TP4.1; also elsewhere on the board
+3V3_PIX: TP5.1; also elsewhere on the board
+3V3_SYS: TP1.1; also elsewhere on the board
+4V5: TP2.1; also elsewhere on the board
GND: TP6.1; also elsewhere on the board

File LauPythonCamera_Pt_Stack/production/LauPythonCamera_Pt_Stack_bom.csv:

Comment,Designator,Footprint,LCSC Part #
1u,"C1,C2,C3,C4,C5,C6,C7",C_0402_1005Metric,C52923
100n,"C8,C9,C10,C11,C26,C27,C28,C38,C40",C_0402_1005Metric,C1525
10n,"C12,C13,C14,C15,C16,C17,C18,C19,C20,C21,C22,C39",C_0402_1005Metric,C15195
10u,"C23,C24,C31,C32,C33",C_0805_2012Metric,C15850
1u,"C29,C30,C34,C35,C36,C37",C_0603_1608Metric,C15849
220n,C41,C_0402_1005Metric,C16772
DF40C-80DP (Bank A),J1,Hirose_DF40C-80DP-0.4V_2x40-1MP_P0.4mm,C294544
DF40C-80DP (Bank B),J2,Hirose_DF40C-80DP-0.4V_2x40-1MP_P0.4mm,C294544
DF40C-50DP (Control),J3,Hirose_DF40C-50DP-0.4V_2x25-1MP_P0.4mm,C424645
2.2uH,L1,L_Power_4x4mm_SMNR4020,C135262
47k,R1,R_0402_1005Metric,C25792
100R,R2,R_0402_1005Metric,C25076
10k,"R3,R4,R5,R6,R7,R12,R13,R14",R_0402_1005Metric,C25744
330k,R8,R_0402_1005Metric,C25778
51k,R9,R_0402_1005Metric,C25794
1k,"R10,R11,R17",R_0402_1005Metric,C11702
100k,"R15,R16",R_0402_1005Metric,C25741
NOIP1SN1300A-QTI,U1,Andon_680-48-SM-G10-R14,
TPS7A2018PDBVR,U2,SOT-23-5,C963430
TPS61023DRLR,U3,SOT-563,C919459
TPS7A2033PDBVR,"U4,U5",SOT-23-5,C2862740
TLV803SDBZR,"U6,U7",SOT-23,C132016
